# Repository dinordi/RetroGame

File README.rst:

Retro Game - Saga of Sacrifice
******************************

.. raw:: html

   <a href="https://github.com/dinordi/RetroGame/">
     <p align="center">
       <picture>
         <source media="(prefers-color-scheme: dark)" srcset="images/readme/player.png">
         <source media="(prefers-color-scheme: light)" srcset="images/readme/player.png">
         
       </picture>
     </p>
   </a>

Saga of Sacrifice is a 2D-platformer where the player traverses several levels to defeat his nemesis, a samurai.

The game runs using a ESP32-S3-DevkitC v1.1 and a Basys3 FPGA.

Video Showing Gameplay
**********************

.. image:: https://img.youtube.com/vi/o0PvoIunmNI/maxresdefault.jpg
    :alt: IMAGE ALT TEXT HERE
    :target: https://www.youtube.com/watch?v=o0PvoIunmNI

Getting Started
***************

Welcome to Saga of Sacrifice! See the `Hardware Documentation`_ for a high-level overview,
and the documentation's `Setup`_ to get the game running.

.. start_include_here

.. _project-resources:

Hardware Documentation
**********************

The KiCad files can be downloaded from the Docs/KiCad folder.

`Scheme <https://github.com/dinordi/RetroGame/blob/main/Docs/KiCad/images/retrogame.pdf>`_

`PCB Coloured <https://github.com/dinordi/RetroGame/blob/main/Docs/KiCad/images/retrogame-brd.svg>`_

`PCB Back <https://github.com/dinordi/RetroGame/blob/main/Docs/KiCad/images/PCBAchter.pdf>`_

`PCB Front <https://github.com/dinordi/RetroGame/blob/main/Docs/KiCad/images/PCBVoor.pdf>`_

+------------------+----------------------------------+
| GPIO pin         | Function                         |
+==================+==================================+
| GPIO 6           | Joystick left                    |
+------------------+----------------------------------+
| GPIO 4           | Joystick right                   |
+------------------+----------------------------------+
| GPIO 7           | Joystick up                      |
+------------------+----------------------------------+
| GPIO 5           | Joystick down                    |
+------------------+----------------------------------+
| GPIO 16          | Green button                     |
+------------------+----------------------------------+
| GPIO 15          | Red button                       |
+------------------+----------------------------------+
| GPIO 9           | Black button                     |
+------------------+----------------------------------+

Setup
*****

The game runs on a ESP32-S3-Devkit-C v1.1 using the Zephyr RTOS. v3.5.0.
Windows 11 is tested no guarantee is given for any other OS. For building the esp code West version: v1.2.0 is used.
For compiling the FPGA code Vivado 2023.2 is used.
Plug the VGA cable into the FPGA, headphonejack into the aux output and the micro usb cables into the ESP32 and FPGA.
That should be all for the setup, the software is already flashed.

DFPlayer mini
*************

If at any point the music/SFX need to be changed. The SD Card folder structure must be maintained!

Software
*************

The game is written in C++, classdiagram is available in the Docs folder.
The source code for the game is well-commented, providing clear explanations for the functionality of each function. 
With some research and understanding of these comments, you should be able to modify and adapt the code to suit your needs.

Changing Sprites
****************

explanation how to change sprites with Piksel and which dimensions we use (15x15 etc)
and also how to upload them to the FPGA.

Changing text
**************

explanation how to change text in code.
Frequently Asked Questions (FAQ)
---------------------------------

**Q: How to fix empty screen/weird boxes are all over the screen?**

A: Restart ESP32 using reset button or unplugging from power. If that does not work, restart FPGA by pressing the restart button.

**Q: Why isn't there any audio playing?**

A: Check if both SD cards are seated properly in DFPlayer mini's. Also check if the aux cable is connected to an amplified speaker.
The aux connection port could be a little janky, so check if the GND pin makes connection to the PCB.

**Q: Can't flash or can't see the COM port for the esp?**

A: Make sure you have the micro usb cable in the port labeled 'uart' on the esp. Also installing a driver is needed to get the COM port to work.
Download the driver in the github and follow the following link starting at "Manually Install Device Drivers on Windows". `Manually Install Device Drivers on Windows`_ 
When you browse for the driver, select the driver folder from the git.

Additional Resources
--------------------
  | 🌐 `Zephyr Project Website`_

.. 
.. _Zephyr Project Website: https://www.zephyrproject.org
.. _Manually Install Device Drivers on Windows: https://www.groovypost.com/howto/install-device-drivers-manually-on-windows-11-10/
.. _Hardware Documentation: https://github.com/dinordi/RetroGame/tree/main/Docs/
.. _Getting Started Guide: https://github.com/dinordi/RetroGame/tree/main/Docs/
.. _FAQ: https://github.com/dinordi/RetroGame/tree/main/Docs/

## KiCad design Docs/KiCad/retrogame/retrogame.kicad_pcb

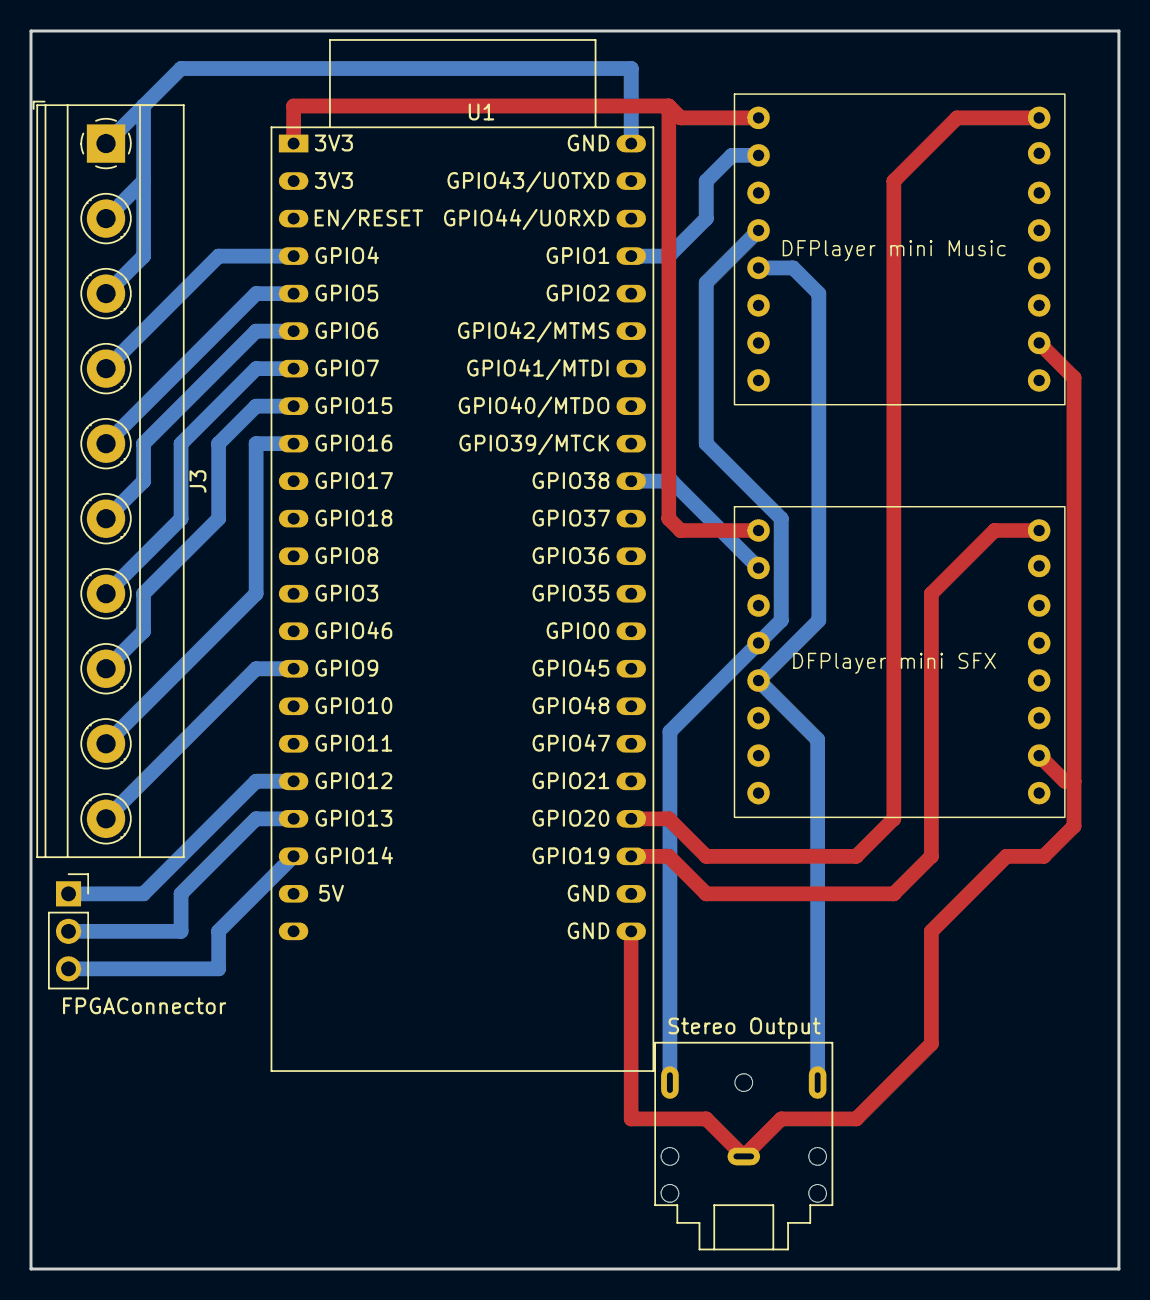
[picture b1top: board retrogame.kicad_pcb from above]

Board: 2 copper layers, 73.7 x 83.8 mm, 6 parts (0 on the bottom side), 18 nets.

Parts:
DFPlayer mini Music: DFPlayer Mini
DFPlayer mini SFX: DFPlayer Mini
FPGAConnector: Conn_01x03_Socket; PinSocket_1x03_P2.54mm_Vertical
J3: Screw_Terminal_01x10; TerminalBlock_Phoenix_MKDS-1,5-10-5.08_1x10_P5.08mm_Horizon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
Stereo Output: AudioJack3; Jack_3.5mm_CUI_SJ1-3523N_Horizontal
U1: ESP32-S3-DevKitC

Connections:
/DAC_L: DFPlayer mini Music.5 (DAC_L), DFPlayer mini SFX.5 (DAC_L), Stereo Output.T
/DAC_R: DFPlayer mini Music.4 (DAC_R), DFPlayer mini SFX.4 (DAC_R), Stereo Output.R
/GND: DFPlayer mini Music.10 (GND), DFPlayer mini SFX.10 (GND), J3.8, J3.9, J3.10, Stereo Output.S, U1.22 (GND), U1.23 (GND), U1.24 (GND), U1.44 (GND)
/VCC: DFPlayer mini Music.1 (VCC), DFPlayer mini SFX.1 (VCC), U1.1 (3V3), U1.2 (3V3)
unnamed: FPGAConnector.1, U1.18 (GPIO12/ADC2_CH1)
unnamed: FPGAConnector.2, U1.19 (GPIO13/ADC2_CH2)
unnamed: FPGAConnector.3, U1.20 (GPIO14/ADC2_CH3)
unnamed: J3.1, U1.15 (GPIO9/ADC1_CH8)
unnamed: J3.2, U1.9 (GPIO16/ADC2_CH5/32K_N)
unnamed: J3.3, U1.8 (GPIO15/ADC2_CH4/32K_P)
unnamed: J3.4, U1.7 (GPIO7/ADC1_CH6)
unnamed: J3.5, U1.6 (GPIO6/ADC1_CH5)
unnamed: J3.6, U1.5 (GPIO5/ADC1_CH4)
unnamed: J3.7, U1.4 (GPIO4/ADC1_CH3)
unnamed: DFPlayer mini Music.2 (RX), U1.41 (GPIO1/ADC1_CH0)
unnamed: DFPlayer mini SFX.16 (BUSY), U1.25 (GPIO19/USB_D-)
unnamed: DFPlayer mini Music.16 (BUSY), U1.26 (GPIO20/USB_D+)
unnamed: DFPlayer mini SFX.2 (RX), U1.35 (GPIO38)

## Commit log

2024-02-06 First upload
2024-02-06 Added gitignore
2024-02-08 Added ADC and button handlers
2024-02-08 Changed readme and gitignore
2024-02-08 Changed gitignore
2024-02-08 Added FPGA uart commands and improved logic for shooting
2024-02-08 enabled serial and uart interrupt in project config
2024-02-22 Last lightgun concept commit
2024-02-23 Removed adc class from program
2024-02-23 eerste versie VHDL
2024-02-27 remove folder structure
2024-02-29 SPI working
2024-03-01 Can add entities to game and send out locations over SPI
2024-03-01 fixed overlay file button + spi2
2024-03-01 Can send over SPI with 10MHz
2024-03-01 Converted to account for switched 8 bit words. Sends 150 entities with ID 1-10
2024-03-04 Changed SPI frequency to 10MHz
2024-03-04 Updated button handler and it now can handle 4 button inputs
2024-03-06 first version full project no test done
2024-03-07 Update README.rst
    Added GPIO description
2024-03-07 added fpga bit check
2024-03-07 background coe file added
2024-03-07 1 entity moves across part of screen
2024-03-07 Updated VHDL to work from github
2024-03-07 Working background - no sprite
2024-03-08 Can read all buttons and character moves with buttons
    Using the buttons the entity will move left and right on the screen in between x 350 and x 0
2024-03-10 Changed VHDL to microblaze version
2024-03-10 Added VitisWorkspace with Vitis classic project
2024-03-11 Last version microblaze
2024-03-11 first working version display
2024-03-11 Can properly read input
2024-03-11 Added 3131 sprite
2024-03-12 Entity can have certain animations
2024-03-13 Added gravity but still need collision
2024-03-13 Can 'walk' left to right
2024-03-13 ANIMATIONS
2024-03-13 Added new GPU and added new platform handler
2024-03-13 Added new gpu and removed old
2024-03-13 BugFix
2024-03-13 Can walk left to right with platforms
2024-03-13 Walking direction inverted
2024-03-13 100 long array bitsream
2024-03-14 Fixed right side popping and partly leftside. Also added gravity
2024-03-27 Using input pullup instead of external resistor
2024-03-29 Reversed button polarity and added frame Counter to Game()
2024-03-29 FPGA now supports new animations and text
2024-03-29 Added main menu and gameState manager
2024-03-29 added audio functionalities
2024-03-29 moved tick function to game
2024-03-30 made tick function modulair and delete Game from constructors
2024-03-30 Improved menu navigation. Still needs a more clean solution
2024-03-30 Changed tick function name to update. Changed update function name to updateGame
2024-03-30 Double function declaration for updateGame()
2024-03-30 Double function declaration for updateSelection()
2024-03-30 added stop functionalities, fixed buffer reading
2024-03-31 added object class
2024-04-01 changed drawlevel function, now prints all actors on screen
2024-04-01 Player has shooting animation when holding atk button
2024-04-01 added physical bullet
2024-04-01 Changed atk button to GPIO45
2024-04-01 added .cache file into gitignore
2024-04-01 added virtual AttackCheck function for attack sprite offset
2024-04-01 Changed Y value to actorY instead of getY()
2024-04-01 Added counter for attack animation on rising edge
2024-04-01 added behaviour
2024-04-01 Changed animation speed of shooting and idle
2024-04-01 added all needed functionalities to w/r to esp32 internal flash
2024-04-01 Added samurai class with animations
2024-04-01 Removed samurai from call in constructor
2024-04-02 removed frames++ call in updateGame()
2024-04-02 Changed pins to final product
2024-04-02 Changed pins to match PCB layout
2024-04-02 fade out and fade in added
2024-04-02 Fixed uart overlay call
2024-04-02 added collision no damage yet
2024-04-02 Game starts with menu music
2024-04-02 added damage for collision on enemy
2024-04-03 Added fatbat
2024-04-03 Removed printk calls
2024-04-03 added hit animation for the fatbat enemy
2024-04-03 fixed enemies damaging eachother and fixed enemies not dying
2024-04-03 Added some samurai behaviour
2024-04-03 commented out printk statements
2024-04-03 added highscore and score tracking functionalities, required additional includements of flash_esp classes
2024-04-03 added the hit animation to the player and to the samurai
2024-04-03 initiële-waarde-toegevoegd
2024-04-03 Removed printk calls and changed samurai behaviour
2024-04-03 Moved right border to 1530 and added attackingPlayer state for samurai
2024-04-03 added feature dead and fixed some bugs
2024-04-03 higscore functionality added to game main menu
2024-04-03 added the spawning of enemies per level as well as maximum enemies on screen
2024-04-03 added dead screen
2024-04-03 Added new levels
2024-04-03 Adde last GPU version
2024-04-03 Added images/coe files
2024-04-03 Fatbat now turns around at borders
2024-04-03 added time multiplier and level complete score
2024-04-03 Removed print call in menu
2024-04-03 added the randomness in the movement of fatbats
2024-04-03 removed some prints
2024-04-03 fixed stack issues
2024-04-03 removed unnecessary libraries
2024-04-03 fixed movement of fatbat
2024-04-03 added bob mode and reset live and killed enemies
2024-04-04 uncommented random
2024-04-04 added platform range get and werewolfman
2024-04-04 fixed weird behaviour around the border of the game
2024-04-04 Removed dynamic casting
2024-04-04 Added workspace
2024-04-04 added player score not detecting higscore yet because compare is not being executed
2024-04-04 Fixed animation offset
2024-04-04 Removed Entity getType
2024-04-04 merged staticcasting branch to dev2
2024-04-04 Game starts with vectors
2024-04-04 eerst deel heap mmu
2024-04-04 Bullets no work
2024-04-04 Bullets working
2024-04-04 fixing string issue's in get leaderboard
2024-04-04 Changed object->y to getY()
2024-04-04 Made fatbats random
2024-04-04 added values so respawn works
2024-04-04 Added samurai to game-- no behaviour
2024-04-04 C strings converted to c++ strings
2024-04-04 Removed instant bossfight
2024-04-04 Samurai not game breaking
2024-04-04 Samurai will kill you
2024-04-04 added not working werewolf
2024-04-04 feature added where the highscore menu gets overwritten with new highscores
2024-04-04 removed libraries prj.conf
2024-04-04 werewolf working no attack yet
2024-04-04 points modified
2024-04-04 Fixed nextlevel
2024-04-04 Wherewolf Y fixed
2024-04-05 think everything is working
2024-04-05 Added teleporter
2024-04-05 working
2024-04-05 added sfx and music
2024-04-05 bug found can't send too much highscores to screen
2024-04-05 confirmed that bug was being produced in draw highscore
2024-04-05 scores
2024-04-05 Fixed sfx
2024-04-05 Removed prints
2024-04-05 Audio done
2024-04-05 Fixed reset
2024-04-07 shoot button now also jumps
2024-04-07 Can see highscore as you are playing
2024-04-07 Added documentation files
2024-04-07 Added player sprite
2024-04-07 Rename GS.rst to README.rst
2024-04-07 Removed unnecessary readme
2024-04-07 Removed DS
2024-04-07 Added svg
2024-04-07 Update README.rst
    links to docs fixed for main branch
2024-04-08 added classdiagram and question for flashing
2024-04-08 Update README.rst
    piksel -> Piksel
2024-04-08 added last version gpu
2024-04-08 more comments added to audio_module functions
2024-04-08 Button comments
2024-04-15 fixed scores and merged broken audio
2024-04-16 fixed scores
2024-04-19 added binary and build folders
2024-04-20 Fixed GPIO table layout
2024-04-20 Added doxygen for button class
2024-04-20 Added doxygen for actor class
2024-04-20 Added doxygen for fpga class
2024-04-21 added doxygen comments for almost all classes
2024-04-21 added converted comments to doxygen
2024-04-21 changed doxygen comments
2024-04-21 fixed doxygen
2024-04-21 Added doxygen for several files for the files list
2024-12-09 Update README.rst
    Added video
